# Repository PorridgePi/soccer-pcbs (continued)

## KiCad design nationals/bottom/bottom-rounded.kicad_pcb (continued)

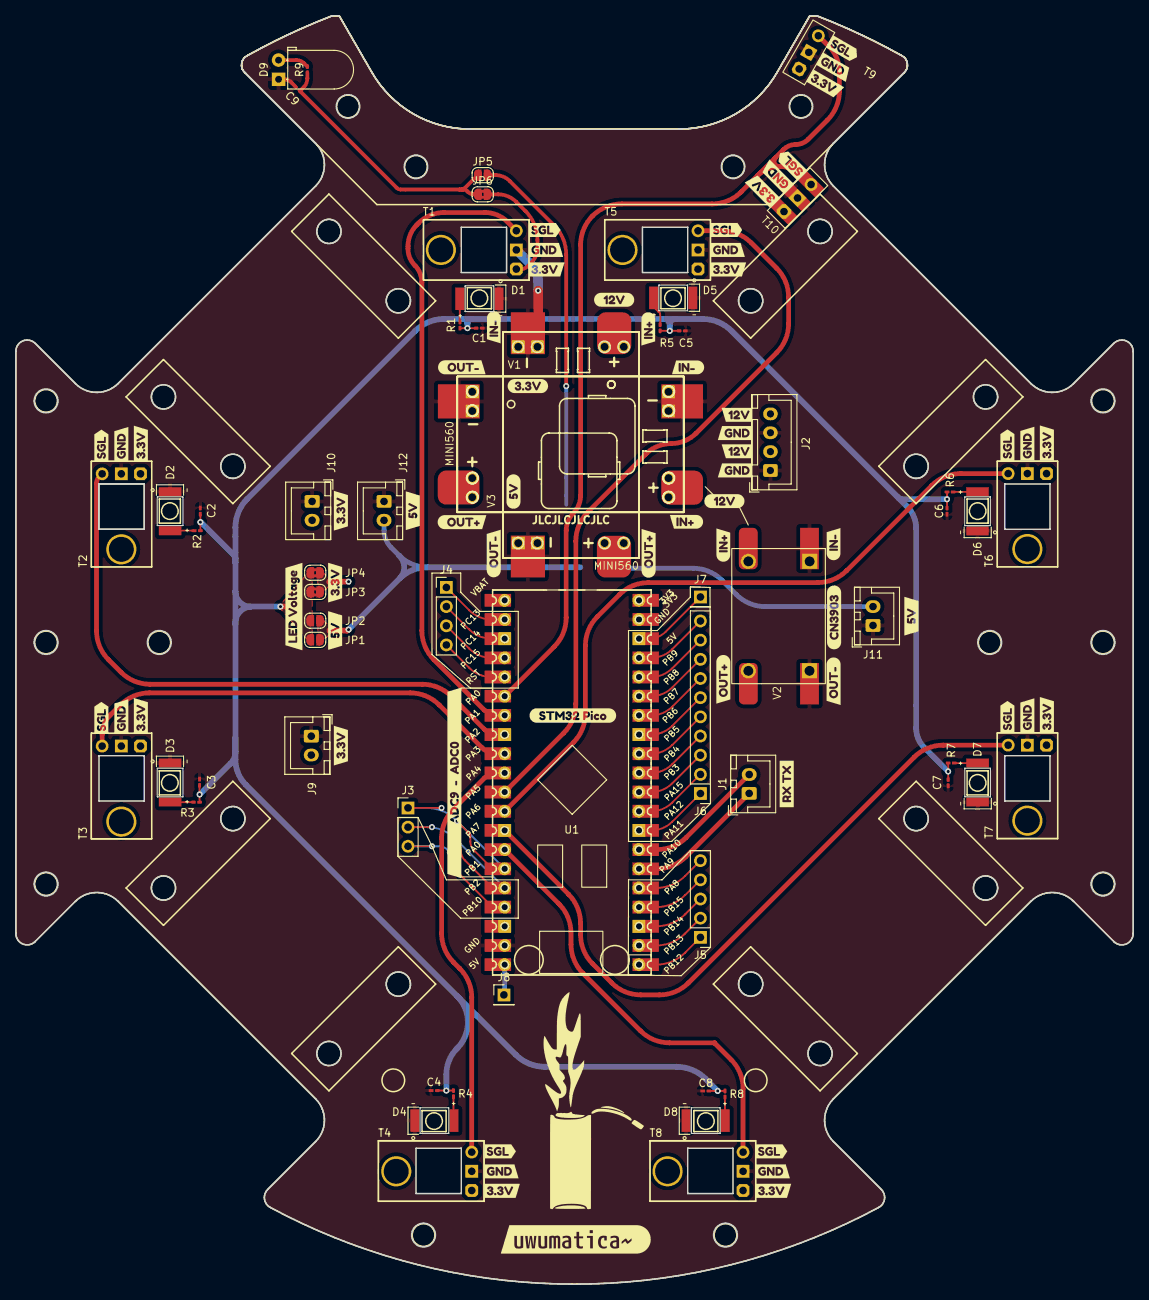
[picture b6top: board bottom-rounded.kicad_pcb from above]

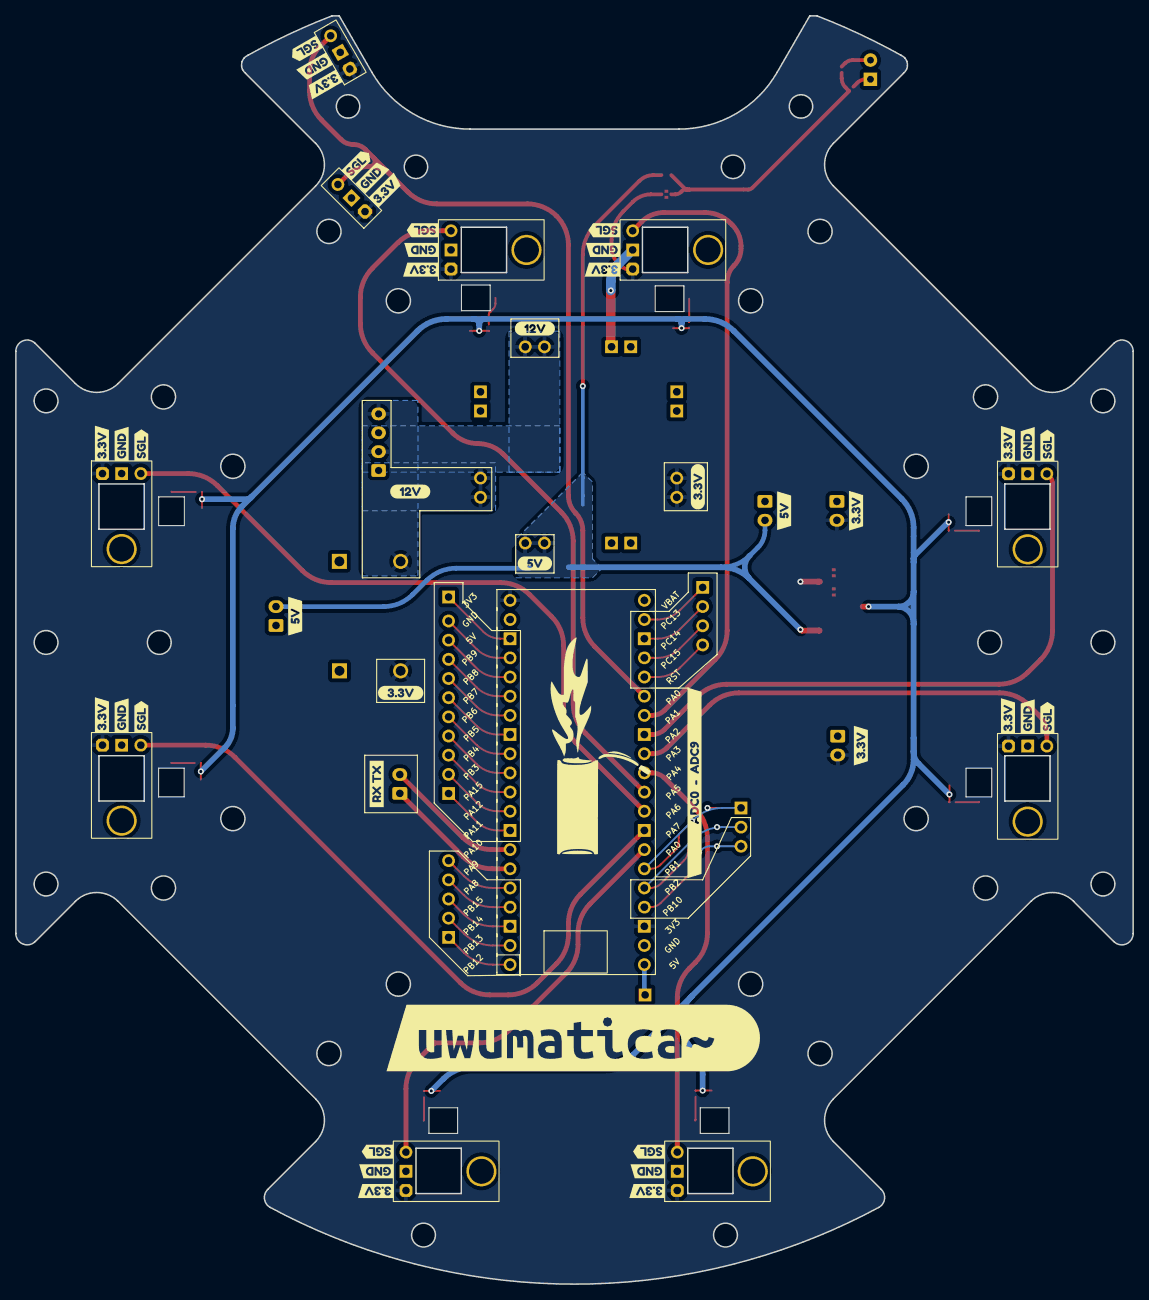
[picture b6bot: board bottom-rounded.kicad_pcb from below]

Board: 2 copper layers, 148.0 x 168.0 mm, 87 parts (11 on the bottom side), 50 nets.

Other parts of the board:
kibuzzard-6594DF00: G***; kibuzzard-6594DF00
kibuzzard-6594DF24, kibuzzard-6594DF24#2, kibuzzard-6594DF24#3, kibuzzard-6594DF24#4, kibuzzard-6594DF24#5: G***; kibuzzard-6594DF24
kibuzzard-6594DF35, kibuzzard-6594DF35#2, kibuzzard-6594DF35#3, kibuzzard-6594DF35#4, kibuzzard-6594DF35#5: G***; kibuzzard-6594DF35
kibuzzard-6594E3AA: G***; kibuzzard-6594E3AA
kibuzzard-6594E48C, kibuzzard-6594E48C#2: G***; kibuzzard-6594E48C
kibuzzard-6594E396: G***; kibuzzard-6594E396
kibuzzard-6594E501, kibuzzard-6594E501#2: G***; kibuzzard-6594E501
kibuzzard-6594EB95, kibuzzard-6594EB95#2, kibuzzard-6594EB95#3, kibuzzard-6594EB95#4: G***; kibuzzard-6594EB95
kibuzzard-6594EC8D, kibuzzard-6594EC8D#2: G***; kibuzzard-6594EC8D
kibuzzard-6594ED36: G***; kibuzzard-6594ED36
kibuzzard-6594F15C, kibuzzard-6594F15C#2: G***; kibuzzard-6594F15C
kibuzzard-659511C4: G***; kibuzzard-659511C4
kibuzzard-659511D9: G***; kibuzzard-659511D9

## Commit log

2024-04-28 gitignore: feat: add gitignore
2024-04-29 footprints: feat: add footprints
2024-04-29 symbols: feat: add symbols
2024-04-29 pcbs: feat: add bottom plate
2024-04-29 pcbs: feat: add top plate
2024-04-29 pcbs: feat: add imu plate
2024-04-29 chore: organise files into subdirectories
2024-04-29 libs: feat: add KiCAD libraries as submodule
2024-04-29 gitignore: feat: use globstar and add auto_saved_files
2024-04-30 pcbs: feat: add prototype pcb with gerber and SMT assembly files
2024-05-20 pcbs: feat: updated schematics with pdf
2024-05-30 diagrams: feat: add bot diagram
2024-06-02 diagrams: feat: update bot diagram
2024-06-06 pcbs: feat: add power plate schematics
2024-06-07 libs: chore: update libraries
2024-06-07 pcbs: feat: add bottom plate schematics with TEMTs
2024-06-07 pcbs: feat: update and complete bottom plate schematics
2024-06-07 gitignore: feat: add KiCAD lock files
2024-06-08 pcbs: bottom: fix: incorrect label directions and use UART pins
2024-06-08 pcbs: top: feat: add incomplete schematics
2024-06-08 pcbs: chore: update date, single schematics output folder
2024-06-08 pcbs: bottom: fix: label directions
2024-06-08 pcbs: top: feat: updated schematics
2024-06-08 pcbs: bottom: feat: add spare 3.3V JSTs to schematics
2024-06-08 pcbs: bottom: feat: add pull-up resistor for RUN
2024-06-08 pcbs: chore: update schematic exports
2024-06-08 pcbs: top: feat: add buttons
2024-06-08 pcbs: top: fix: missing footprint in schematics
2024-06-09 pcbs: imu: feat: add IMU plate schematics
2024-06-09 pcbs: power: feat: organise schematics
2024-06-09 pcbs: imu: feat: add buttons to schematics
2024-06-12 cad: feat: add bottom plate dxf
2024-06-12 pcbs: bottom: feat: add mounting holes in schematics and swap labels
2024-06-12 cad: feat: add bottom plate outline dxf
2024-06-12 pcbs: bottom: feat: add pcb with parts placed, left with routing
2024-06-12 pcbs: bottom: feat: plot updated schematics
2024-06-12 pcbs: bottom: feat: complete pcb routing, update schematics with better TEMT allocation
2024-06-13 pcbs: bottom: feat: complete pcb deco
2024-06-13 pcbs: bottom: feat: cleanup pcb
2024-06-13 pcbs: bottom: feat: add pcb with round tracks
2024-06-13 pcbs: bottom: fix: remove via in pads
2024-06-14 pcbs: bottom: fix: add JLCJLCJLC text
2024-06-14 pcbs: bottom: chore: update PCB with tracks rounded
2024-06-14 pcbs: bottom: feat: add gerber, BOM and CPL files
2024-06-14 chore: remove temporary files
2024-06-14 pcbs: imu: fix: 2 pin instead of 4 pin JST
2024-06-14 chore: update backup files
2024-06-14 !chore: move pcbs into subdirectory
2024-06-14 chore: move diagrams into internationals subdirectory
2024-06-14 chore: move libs into internationals subdirectory
2024-06-14 chore: move prototype into subdirectory
2024-06-14 chore: update libs directory in config
2024-06-14 chore: cleanup and update symbols config
2024-06-14 chore: move symbols into nationals subdirectory
2024-06-14 bom: feat: add BOM for all 4 plates and update KiCAD config
2024-06-14 chore: move prototype schematics PDF
2024-06-15 pcbs: top: feat: import dxf
2024-06-15 pcbs: bottom: fix: use horizontal JST and update SW numbers in schematics
2024-06-15 pcbs: top: feat: add mounting holes to schematics and remove GND from USB pad
2024-06-15 pcbs: top: feat: complete pcb
2024-06-15 pcbs: top: feat: plot updated schematics
2024-06-15 pcbs: top: feat: add pcb with tracks rounded
2024-06-17 pcbs: power: feat: add mounting holes to schematics
2024-06-17 pcbs: power: feat: add pcb v1
2024-06-17 pcbs: power: feat: complete solder mask and silkscreen
2024-06-17 pcbs: power: feat: add gerbers
2024-06-17 pcbs: top: feat: add JLCJLCJLCJLC silkscreen
2024-06-17 pcbs: power: fix: increased copper area and update gerber
2024-06-17 pcbs: top: chore: generate round tracks and gerbers
2024-06-17 pcbs: imu: feat: add I2C pull-ups and IMU voltage selector
2024-06-17 pcbs: imu: feat: add completed pcb
2024-06-17 pcbs: imu: feat: add pcb with tracks rounded
2024-06-17 pcbs: imu: feat: add gerbers
2024-06-17 pcbs: feat: add OSHW and Rust Ferris logos
2024-07-01 pcbs: bottom: !fix: remove via shorting trace to GND
2024-07-01 pcbs: bottom: fix: update 0603 10k R LCSC number
2024-07-01 pcbs: bottom: feat: add updated gerber without short
2024-07-01 README: feat: add README for internationals
2024-07-01 README: feat: update internationals README with example
